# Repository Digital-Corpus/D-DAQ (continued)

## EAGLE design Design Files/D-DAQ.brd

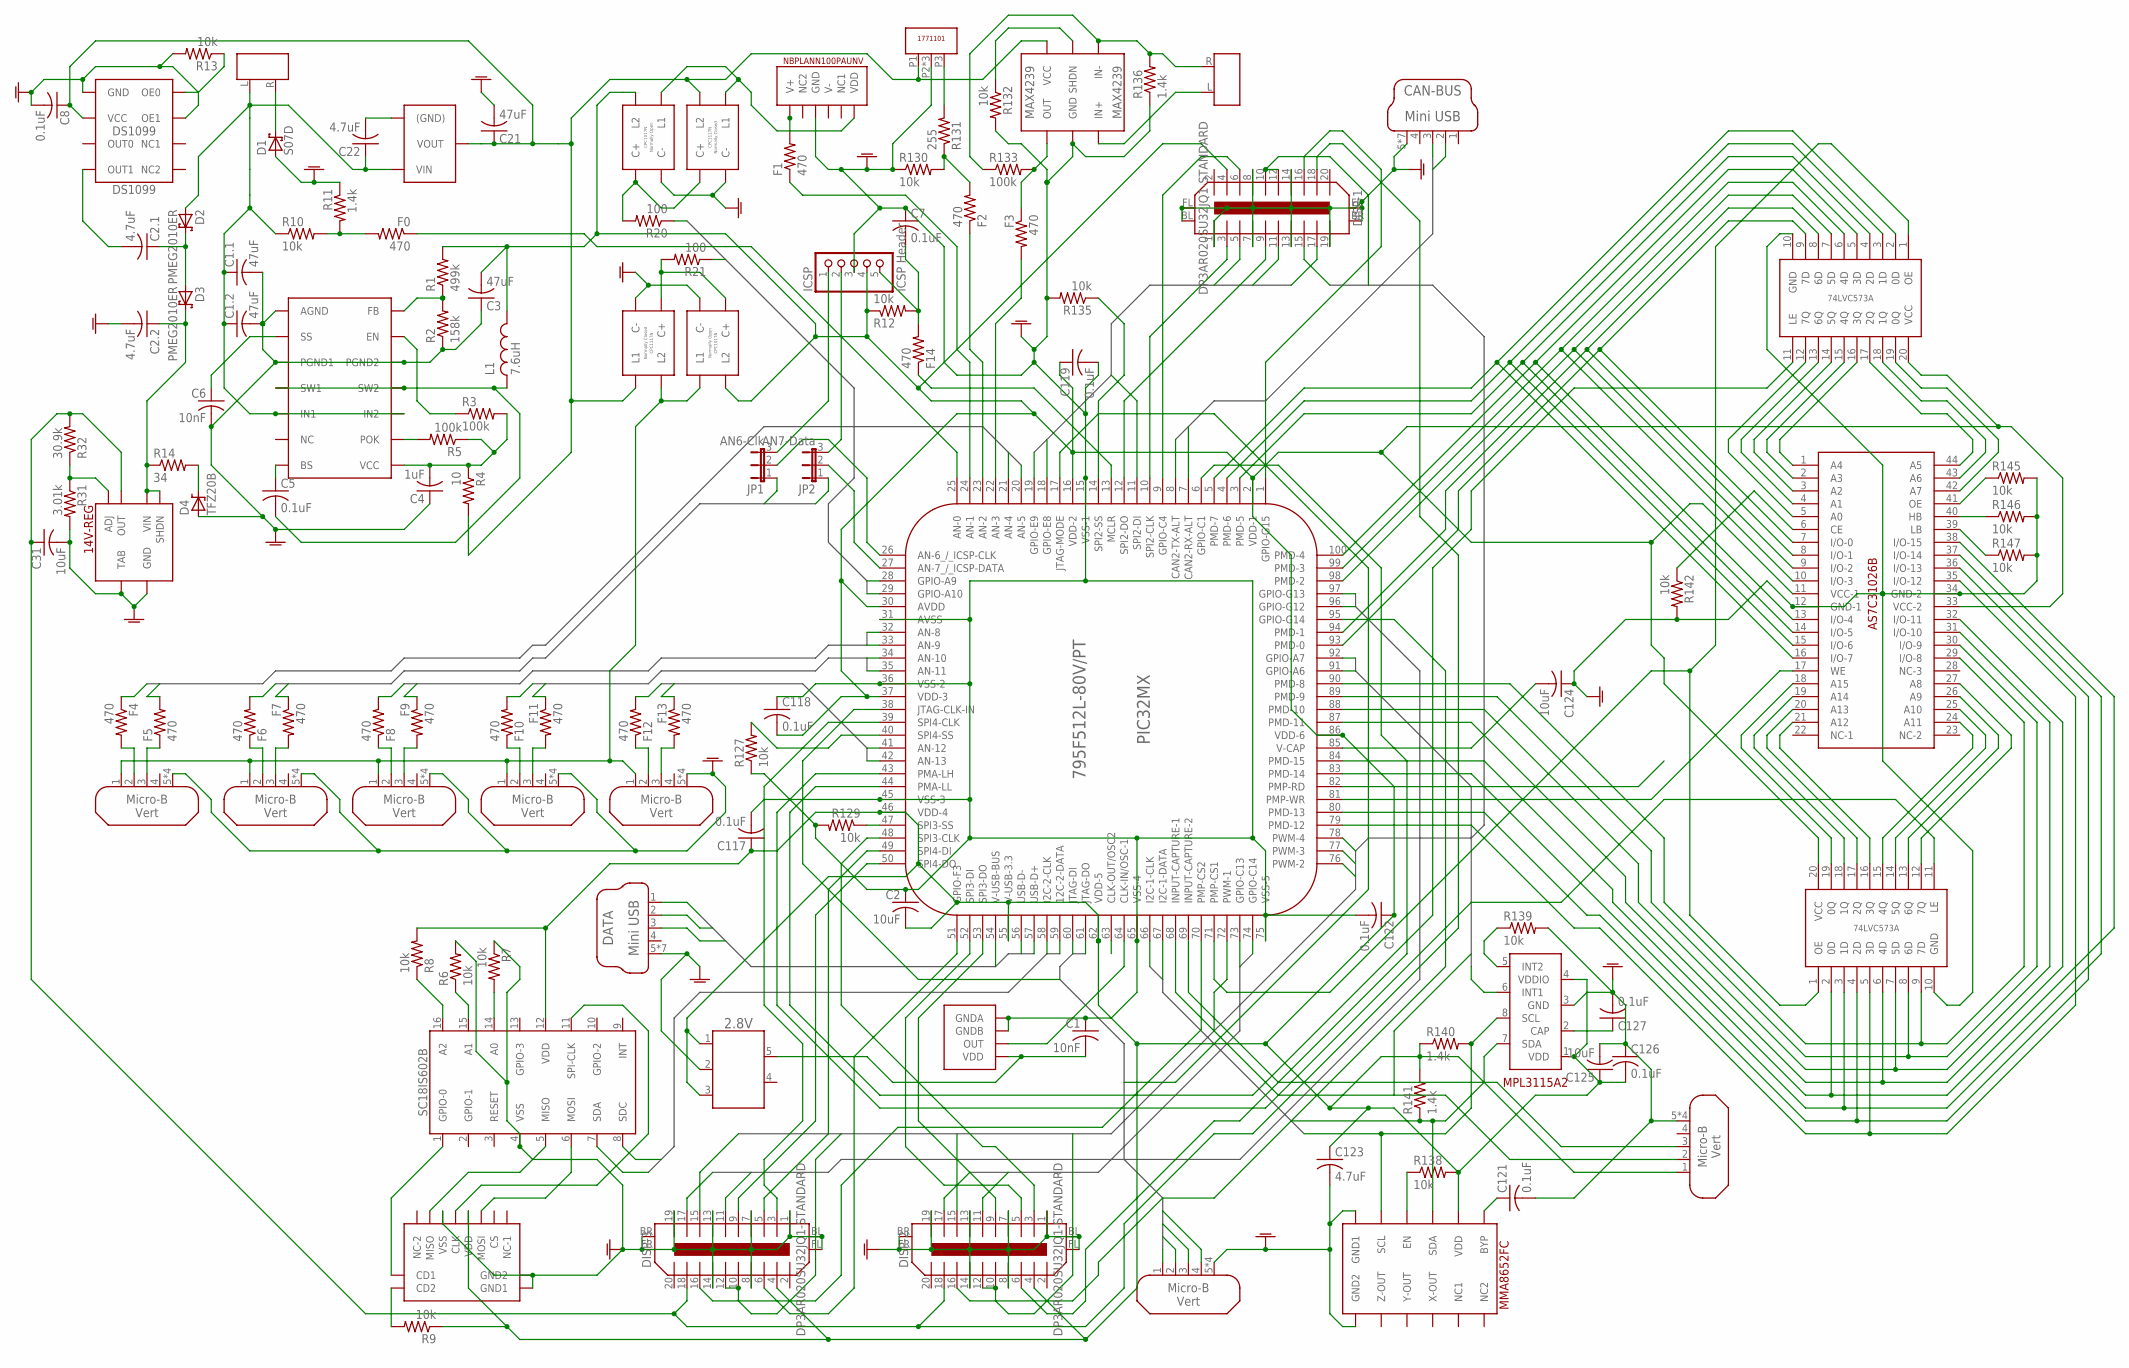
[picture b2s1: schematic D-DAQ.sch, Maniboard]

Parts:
2.8V: TC1016; SOT-23-5
3.3V-TOGGLE-1, 3.3V-TOGGLE-2: NO SSR; SOP-4--CPC1017N
4&5, 6&7, 8&9, 10&11, 12&13: Micro USB; USB-MICRO-B-VERT
5V-REG: ZLDO1117-5.0; SOT-223-5
5V-TOGGLE-1, 5V-TOGGLE-2: NC SSR; SOP-4--CPC1117N
14V-REG: TL1963A-33DCQ; SOT-223-6
AS7C31026B: 1 Mbit SRAM; TSOP-44
AUX-PRESS: PC-1771101
C1, C6: 10nF; C0603K
C1.1, C1.2, C3, C21: 47uF; C1206
C2, C124, C125: 10uF; C0603K
C2.1, C2.2, C22: 4.7uF; C1206
C4: 1uF; C0603K
C5, C7, C8, C117, C118, C119, C121, C122, C126, C127: 0.1uF; C0603K
C31: 10uF; C1206
C123: 4.7uF; C0603K
CAN-BUS: Mini USB; USB-MINI-B-VERT
D1: S07D; SOD-123W
D2, D3: PMEG2010ER; SOD-123W
D4: TFZ20B; TUMD2
DATA: Mini USB; USB-MINI-B-VERT
DISP-1, DISP-2, DISP-3: DP3AR020SU32JQ1-STANDARD
EGT: 1702610; PC-1702610
EGT-AMP: MAX4239; SOT-8
F0, F1, F2, F3, F4, F5, F6, F7, F8, F9, F10, F11, F12, F13, F14: 470; R0603
ICSP: ICSP Header; 1X05
IMP.: Micro USB; USB-MICRO-B-VERT
JP1: AN6-Clk; JP2
JP2: AN7-Data; JP2
JTAG: Micro USB; USB-MICRO-B-VERT
L1: 7.6uH; 7443551XXX
LATCH-HIGH: Octal D-Latch; TSSOP-20
LATCH-LOW: Octal D-Latch; TSSOP-20
MAIN-SMPS: MP2209; QFN-14
MICRO-SD: SCHA4B0400
MMA8652FC: Accelerometer; QFN-12
MPL3115A101: Baro & Temp; LGA-8
NBPLANN100PAUNV: Boost; LEADLESS-SMT
PIC32MX: 795F512L-80V/PT; TQFP-100
POWER: 1702610; PC-1702610
R1: 499k; R0603
R2: 158k; R0603
R3, R5, R133: 100k; R0603
R4: 10; R0603
R6, R7, R8, R9, R10, R12, R13, R127, R129, R130, R132, R135, R138, R139, R142, R145, R146, R147: 10k; R0603
R11, R136, R140, R141: 1.4k; R0603
R14: 34; R0603
R20, R21: 100; R0603
R31: 3.01k; R0603
R32: 30.9k; R0603
R131: 255; R0603
SC18IS602B: I2C to SPI; TSSOP-16
Y1: 16.368 MHz; XTC7009
Y2: DS1099; SOIC-8

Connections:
3.3-&-5V-TOGGLE1: PIC32MX.28 (GPIO-A9), R21.1
3.3-&-5V-TOGGLE2: PIC32MX.29 (GPIO-A10), R20.1
3.3V-RAIL: 2.8V.1 (V-IN), 2.8V.3 (SHDN), 3.3V-TOGGLE-1.4 (L2), 3.3V-TOGGLE-2.4 (L2), AS7C31026B.11 (VCC-1), AS7C31026B.33 (VCC-2), C2.2, C3.2, C117.1, C118.2, C119.1, C122.1, C123.1, C125.1, C126.2, DISP-1.4, DISP-2.4, DISP-3.4, ICSP.4, IMP..1, L1.P$2, LATCH-HIGH.20 (VCC), LATCH-LOW.20 (VCC), MICRO-SD.4 (VDD), MMA8652FC.2 (VDD), MPL3115A101.1 (VDD), MPL3115A101.4 (VDDIO), PIC32MX.2 (VDD-1), PIC32MX.16 (VDD-2), PIC32MX.30 (AVDD), PIC32MX.37 (VDD-3), PIC32MX.46 (VDD-4), PIC32MX.55 (V-USB-3.3), PIC32MX.62 (VDD-5), PIC32MX.86 (VDD-6), R1.2, R8.2, R9.1, R12.1, R138.2, R140.1, R141.2, SC18IS602B.12 (VDD)
5V-ADJ: 5V-REG.ADJ ((GND)), C22.2
5V-RAIL: 5V-REG.VOUT, 5V-REG.VOUT-1 (VOUT), 5V-TOGGLE-1.3 (L1), 5V-TOGGLE-2.4 (L2), AUX-PRESS.P1, C8.1, C21.1, EGT-AMP.6 (VCC), R4.2, Y2.3 (VCC)
12V-BS: C5.1, MAIN-SMPS.7 (BS)
12V-ENABLE: MAIN-SMPS.13 (EN), R3.1
12V-FB: MAIN-SMPS.P14 (FB), R1.1, R2.2
12V-INPUT: 5V-REG.VIN, C1.1.1, C1.2.1, C22.1, D2.P$2, MAIN-SMPS.5 (IN1), MAIN-SMPS.10 (IN2), POWER.L, R10.1
12V-OK: MAIN-SMPS.9 (POK), R5.2
12V-SS: C6.1, MAIN-SMPS.2 (SS)
12V-SW: C5.2, L1.P$1, MAIN-SMPS.4 (SW1), MAIN-SMPS.11 (SW2)
12V-VCC: C4.2, MAIN-SMPS.8 (VCC), R3.2, R4.1, R5.1
14V-12V-DIVIDER: F0.2, R10.2, R11.2
14V-ADJ: 14V-REG.ADJ, R31.1, R32.1
14V-INPUT: 14V-REG.SHDN, 14V-REG.VIN, C2.2.1, D3.P$1, R14.1
14V-RAIL: 14V-REG.VOUT (OUT), C31.1, DISP-1.18, DISP-2.18, DISP-3.18, R32.2
100-PSI-SENSOR-RES: 3.3V-TOGGLE-2.1 (C+), 5V-TOGGLE-2.1 (C+), R20.2
A0-PD: R7.2, SC18IS602B.14 (A0)
A1-PD: R6.1, SC18IS602B.15 (A1)
A2-PU: R8.1, SC18IS602B.16 (A2)
ACCEL-EN: MMA8652FC.4 (EN), R138.1
ADD-0: AS7C31026B.5 (A0), LATCH-LOW.12 (7Q)
ADD-1: AS7C31026B.4 (A1), LATCH-LOW.13 (6Q)
ADD-2: AS7C31026B.3 (A2), LATCH-LOW.14 (5Q)
ADD-3: AS7C31026B.2 (A3), LATCH-LOW.15 (4Q)
ADD-4: AS7C31026B.1 (A4), LATCH-LOW.16 (3Q)
ADD-5: AS7C31026B.44 (A5), LATCH-LOW.17 (2Q)
ADD-6: AS7C31026B.43 (A6), LATCH-LOW.18 (1Q)
ADD-7: AS7C31026B.42 (A7), LATCH-LOW.19 (0Q)
ADD-8: AS7C31026B.27 (A8), LATCH-HIGH.12 (7Q)
ADD-9: AS7C31026B.26 (A9), LATCH-HIGH.13 (6Q)
ADD-10: AS7C31026B.25 (A10), LATCH-HIGH.14 (5Q)
ADD-11: AS7C31026B.24 (A11), LATCH-HIGH.15 (4Q)
ADD-12: AS7C31026B.21 (A12), LATCH-HIGH.16 (3Q)
ADD-13: AS7C31026B.20 (A13), LATCH-HIGH.17 (2Q)
ADD-14: AS7C31026B.19 (A14), LATCH-HIGH.18 (1Q)
ADD-15: AS7C31026B.18 (A15), LATCH-HIGH.19 (0Q)
AN0-VOLT: F0.1, PIC32MX.25 (AN-0)
AN1-BOOST: F1.1, PIC32MX.24 (AN-1)
AN2-OIL-PESS: F2.1, PIC32MX.23 (AN-2)
AN3-EGT: F3.2, PIC32MX.22 (AN-3)
AN4: 4&5.2, F4.2
AN5: 4&5.3, F5.1
AN6: 6&7.2, F6.1
AN7: 6&7.3, F7.2
AN8: 8&9.2, F8.1
AN9: 8&9.3, F9.2
AN10: 10&11.2, F10.1
AN11: 10&11.3, F11.2
AN12: 12&13.2, F12.1
AN13: 12&13.3, F13.2
AUTO-DETECT: 3.3V-TOGGLE-1.1 (C+), 5V-TOGGLE-1.1 (C+), R21.2
AUX-OUT: F2.2, R130.2, R131.1
BARO-INT2: MPL3115A101.5 (INT2), R139.1
BOOST-OUT: F1.2, NBPLANN100PAUNV.6 (V+)
BOOST-PWR: 3.3V-TOGGLE-2.3 (L1), 5V-TOGGLE-2.3 (L1), NBPLANN100PAUNV.1 (VDD)
CAN-BUS1: CAN-BUS.2, PIC32MX.8 (CAN2-TX-ALT)
CAN-BUS2: CAN-BUS.3, PIC32MX.7 (CAN2-RX-ALT)
CARD-DETECT: MICRO-SD.G3 (CD1), SC18IS602B.1 (GPIO-0)
CE: AS7C31026B.6 (CE), R142.1
CHARG-CAPS: C2.1.2, Y2.1 (OUT1)
CP-PUMP: C2.1.1, D2.P$1, D3.P$2
CPS-INPUT: IMP..2, PIC32MX.68 (INPUT-CAPTURE-1)
CRYSTAL-OUT: PIC32MX.63 (CLK-OUT/OSC2)
DISP1-B1: DISP-1.5, PIC32MX.11 (SPI2-DI)
DISP1-B2: DISP-1.11, PIC32MX.18 (GPIO-E8)
DISP1-B3: DISP-1.17, PIC32MX.19 (GPIO-E9)
DISP2-B1: DISP-2.5, PIC32MX.52 (SPI3-DI)
DISP2-B2: DISP-2.11, PIC32MX.73 (GPIO-C13)
DISP2-B3: DISP-2.17, PIC32MX.74 (GPIO-C14)
DISP2-RS: DISP-2.16, PIC32MX.95 (GPIO-G14)
DISP3-B1: DISP-3.5, PIC32MX.49 (SPI4-DI)
DISP3-B2: DISP-3.11, PIC32MX.96 (GPIO-G12)
DISP3-B3: DISP-3.17, PIC32MX.97 (GPIO-G13)
DISP3-RS: DISP-1.16, PIC32MX.1 (GPIO-G15)
DISP-1_HPD: DISP-1.6, PIC32MX.9 (GPIO-C4)
DISP-HPD2: DISP-2.6, PIC32MX.6 (GPIO-C1)
DISP-HPD3: DISP-3.6, PIC32MX.51 (GPIO-F3)
EGT-NEG-IN: EGT.R, EGT-AMP.4 (IN-), R133.1, R136.2
EGT-OUT: EGT-AMP.1 (OUT), F3.1, R133.2
EGT-POS-IN: EGT.L, EGT-AMP.3 (IN+)
EGT-SHTDWN: EGT-AMP.5 (SHDN), R132.1
GND: 2.8V.2 (GND), 3.3V-TOGGLE-1.2 (C-), 3.3V-TOGGLE-2.2 (C-), 4&5.5, 4&5.T0 (5), 4&5.T1 (5), 4&5.T2 (5), 5V-TOGGLE-1.2 (C-), 5V-TOGGLE-2.2 (C-), 6&7.5, 6&7.T0 (5), 6&7.T1 (5), 6&7.T2 (5), 8&9.5, 8&9.T0 (5), 8&9.T1 (5), 8&9.T2 (5), 10&11.5, 10&11.T0 (5), 10&11.T1 (5), 10&11.T2 (5), 12&13.5, 12&13.T0 (5), 12&13.T1 (5), 12&13.T2 (5), 14V-REG.GND, 14V-REG.TAB, AS7C31026B.12 (GND-1), AS7C31026B.34 (GND-2), AUX-PRESS.P2, AUX-PRESS.T0, AUX-PRESS.T1, C1.1, C1.1.2, C1.2.2, C2.1, C2.2.2, C3.1, C4.1, C6.2, C7.1, C8.2, C21.2, C31.2, C117.2, C118.1, C119.2, C121.2, C122.2, C123.2, C124.1, C125.2, C126.1, C127.2, CAN-BUS.5, CAN-BUS.P$1, CAN-BUS.P$2, CAN-BUS.P$3, CAN-BUS.P$4, CAN-BUS.T0, CAN-BUS.T1, D1.P$2, D4.P$1 (A), DATA.5, DATA.P$1, DATA.P$2, DATA.P$3, DATA.P$4, DATA.T0, DATA.T1, DISP-1.1, DISP-1.7, DISP-1.8, DISP-1.13, DISP-1.14, DISP-1.19, DISP-1.BL, DISP-1.BR, DISP-1.FL, DISP-1.FR, DISP-2.1, DISP-2.7, DISP-2.8, DISP-2.13, DISP-2.14, DISP-2.19, DISP-2.BL, DISP-2.BR, DISP-2.FL, DISP-2.FR, DISP-3.1, DISP-3.7, DISP-3.8, DISP-3.13, DISP-3.14, DISP-3.19, DISP-3.BL, DISP-3.BR, DISP-3.FL, DISP-3.FR, EGT-AMP.2 (GND), ICSP.3, IMP..5, IMP..T0 (5), IMP..T1 (5), IMP..T2 (5), JTAG.5, JTAG.T0 (5), JTAG.T1 (5), JTAG.T2 (5), LATCH-HIGH.10 (GND), LATCH-LOW.10 (GND), MAIN-SMPS.1 (AGND), MAIN-SMPS.3 (PGND1), MAIN-SMPS.12 (PGND2), MAIN-SMPS.P$15 (AGND), MICRO-SD.6 (VSS), MICRO-SD.G1 (GND1), MICRO-SD.G2 (GND2), MMA8652FC.6 (GND1), MMA8652FC.7 (GND2), MPL3115A101.3 (GND), NBPLANN100PAUNV.4 (GND), PIC32MX.15 (VSS-1), PIC32MX.31 (AVSS), PIC32MX.36 (VSS-2), PIC32MX.45 (VSS-3), PIC32MX.65 (VSS-4), PIC32MX.75 (VSS-5), R2.1, R6.2, R7.1, R11.1, R13.2, R31.2, R127.1, R129.2, R130.1, R132.2, R135.2, R136.1, R139.2, R142.2, R145.2, R146.2, R147.2, SC18IS602B.4 (VSS), Y1.P$1 (GNDA), Y1.P$2 (GNDB), Y2.4 (GND), Y2.6 (OE1)
HB: AS7C31026B.40 (HB), R146.1
I2C-INT-BUS-PIN1: MPL3115A101.6 (INT1), PIC32MX.91 (GPIO-A6)
I2C-INT-BUS-PIN2: PIC32MX.92 (GPIO-A7)
I2C-PIN1: MMA8652FC.5 (SCL), MPL3115A101.8 (SCL), PIC32MX.66 (I2C-1-CLK), R140.2
I2C-PIN2: MMA8652FC.3 (SDA), MPL3115A101.7 (SDA), PIC32MX.67 (I2C-1-DATA), R141.1
I2C-SD-PIN1: PIC32MX.58 (I2C-2-CLK), SC18IS602B.8 (SDC)
I2C-SD-PIN2: PIC32MX.59 (12C-2-DATA), SC18IS602B.7 (SDA)
ICSP-CLK: ICSP.1, JP1.3
ICSP-DATA: ICSP.2, JP2.3
ICSP-MCLR: C7.2, F14.2, ICSP.5, R12.2
INPUT-6_/_ICSP-CLK: JP1.2, PIC32MX.26 (AN-6_/_ICSP-CLK)
INPUT-7_/_ICSP-DATA: JP2.2, PIC32MX.27 (AN-7_/_ICSP-DATA)
JTAG-PIN-1: JTAG.1, PIC32MX.17 (JTAG-MODE)
JTAG-PIN-2: JTAG.2, PIC32MX.38 (JTAG-CLK-IN)
JTAG-PIN-3: JTAG.3, PIC32MX.60 (JTAG-DI)
JTAG-PIN-4: JTAG.4, PIC32MX.61 (JTAG-DO)
LB: AS7C31026B.39 (LB), R147.1
LNS-INPUT: IMP..3, PIC32MX.69 (INPUT-CAPTURE-2)
MCLR: F14.1, PIC32MX.13 (MCLR)
MPL-BYP-CAP: C127.1, MPL3115A101.2 (CAP)
unnamed: C121.1, MMA8652FC.1 (BYP)
OE: AS7C31026B.41 (OE), R145.1
OE0: R13.1, Y2.5 (OE0)
OIL-PRESS-OUT: AUX-PRESS.P3, R131.2
OSC-PWR: 2.8V.5 (V-OUT), C1.2, Y1.P$4 (VDD)
OSC-SIG: PIC32MX.64 (CLK-IN/OSC-1), Y1.P$3 (OUT)
P$1: CAN-BUS.1
PMA-CS2: DISP-3.16, PIC32MX.70 (PMP-CS2)
PMA-HL: LATCH-HIGH.11 (LE), PIC32MX.43 (PMA-LH)
PMA-LL: LATCH-LOW.11 (LE), PIC32MX.44 (PMA-LL)
PMD0: AS7C31026B.7 (I/O-0), LATCH-LOW.9 (7D), PIC32MX.93 (PMD-0)
PMD1: AS7C31026B.8 (I/O-1), LATCH-LOW.8 (6D), PIC32MX.94 (PMD-1)
PMD2: AS7C31026B.9 (I/O-2), LATCH-LOW.7 (5D), PIC32MX.98 (PMD-2)
PMD3: AS7C31026B.10 (I/O-3), LATCH-LOW.6 (4D), PIC32MX.99 (PMD-3)
PMD4: AS7C31026B.13 (I/O-4), LATCH-LOW.5 (3D), PIC32MX.100 (PMD-4)
PMD5: AS7C31026B.14 (I/O-5), LATCH-LOW.4 (2D), PIC32MX.3 (PMD-5)
PMD6: AS7C31026B.15 (I/O-6), LATCH-LOW.3 (1D), PIC32MX.4 (PMD-6)
PMD7: AS7C31026B.16 (I/O-7), LATCH-LOW.2 (0D), PIC32MX.5 (PMD-7)
PMD8: AS7C31026B.29 (I/O-8), LATCH-HIGH.9 (7D), PIC32MX.90 (PMD-8)
PMD9: AS7C31026B.30 (I/O-9), LATCH-HIGH.8 (6D), PIC32MX.89 (PMD-9)
PMD10: AS7C31026B.31 (I/O-10), LATCH-HIGH.7 (5D), PIC32MX.88 (PMD-10)
PMD11: AS7C31026B.32 (I/O-11), LATCH-HIGH.6 (4D), PIC32MX.87 (PMD-11)
PMD12: AS7C31026B.35 (I/O-12), LATCH-HIGH.5 (3D), PIC32MX.79 (PMD-12)
PMD13: AS7C31026B.36 (I/O-13), LATCH-HIGH.4 (2D), PIC32MX.80 (PMD-13)
PMD15: AS7C31026B.38 (I/O-15), LATCH-HIGH.2 (0D), PIC32MX.84 (PMD-15)
PMD-14: AS7C31026B.37 (I/O-14), LATCH-HIGH.3 (1D), PIC32MX.83 (PMD-14)
PMD-READ: PIC32MX.82 (PMP-RD)
PMP-CS1: LATCH-HIGH.1 (OE), LATCH-LOW.1 (OE), PIC32MX.71 (PMP-CS1)
PMP-WRITE: AS7C31026B.17 (WE), PIC32MX.81 (PMP-WR)
PWM1: DISP-3.15, PIC32MX.72 (PWM-1)
PWM2: DISP-2.15, PIC32MX.76 (PWM-2)
PWM3: DISP-1.15, PIC32MX.77 (PWM-3)
PWM4: DISP-1.10, DISP-1.12, DISP-2.10, DISP-2.12, DISP-3.10, DISP-3.12, PIC32MX.78 (PWM-4)
PWR-GND: D1.P$1, POWER.R
SD-MISO: MICRO-SD.7 (MISO), SC18IS602B.5 (MISO)
SD-MOSI: MICRO-SD.3 (MOSI), SC18IS602B.6 (MOSI)
SD-PULL-DOWN: MICRO-SD.G4 (CD2), R9.2
SD-SPI-CLK: MICRO-SD.5 (CLK), SC18IS602B.11 (SPI-CLK)
SENSOR_PAIR_AN4: F4.1, PIC32MX.21 (AN-4)
SENSOR_PAIR_AN5: F5.2, PIC32MX.20 (AN-5)
SENSOR_PAIR_AN6: F6.2, JP1.1
SENSOR_PAIR_AN7: F7.1, JP2.1
SENSOR_PAIR_AN8: F8.2, PIC32MX.32 (AN-8)
SENSOR_PAIR_AN9: F9.1, PIC32MX.33 (AN-9)
SENSOR_PAIR_AN10: F10.2, PIC32MX.34 (AN-10)
SENSOR_PAIR_AN11: F11.1, PIC32MX.35 (AN-11)
SENSOR_PAIR_AN12: F12.2, PIC32MX.41 (AN-12)
SENSOR_PAIR_AN13: F13.1, PIC32MX.42 (AN-13)
SHUNT: D4.P$2 (C), R14.2
SPI2-CLK: DISP-1.3, PIC32MX.10 (SPI2-CLK)
SPI2-DATA: DISP-1.9, PIC32MX.12 (SPI2-DO)
SPI2-SS: PIC32MX.14 (SPI2-SS), R135.1
SPI3-CLK: DISP-2.3, PIC32MX.48 (SPI3-CLK)
SPI3-DATA: DISP-2.9, PIC32MX.53 (SPI3-DO)
SPI3-SS: PIC32MX.47 (SPI3-SS), R129.1
SPI4-CLK: DISP-3.3, PIC32MX.39 (SPI4-CLK)
SPI4-DATA: DISP-3.9, PIC32MX.50 (SPI4-DO)
SPI4-SS: PIC32MX.40 (SPI4-SS), R127.2
USB-PIN1: DATA.1, PIC32MX.54 (V-USB-BUS)
USB-PIN2: DATA.2, PIC32MX.56 (USB-D-)
USB-PIN3: DATA.3, PIC32MX.57 (USB-D+)
USB-PWR: 3.3V-TOGGLE-1.3 (L1), 4&5.1, 5V-TOGGLE-1.4 (L2), 6&7.1, 8&9.1, 10&11.1, 12&13.1
V-CAP: C124.2, PIC32MX.85 (V-CAP)

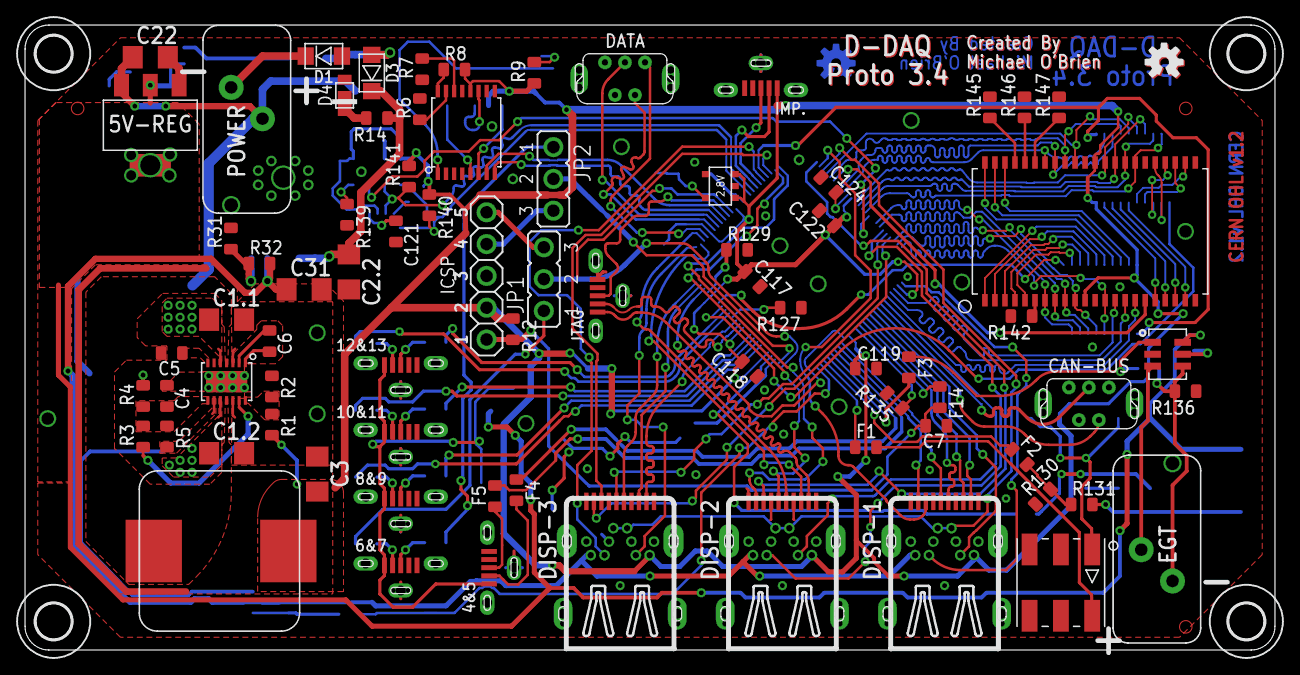
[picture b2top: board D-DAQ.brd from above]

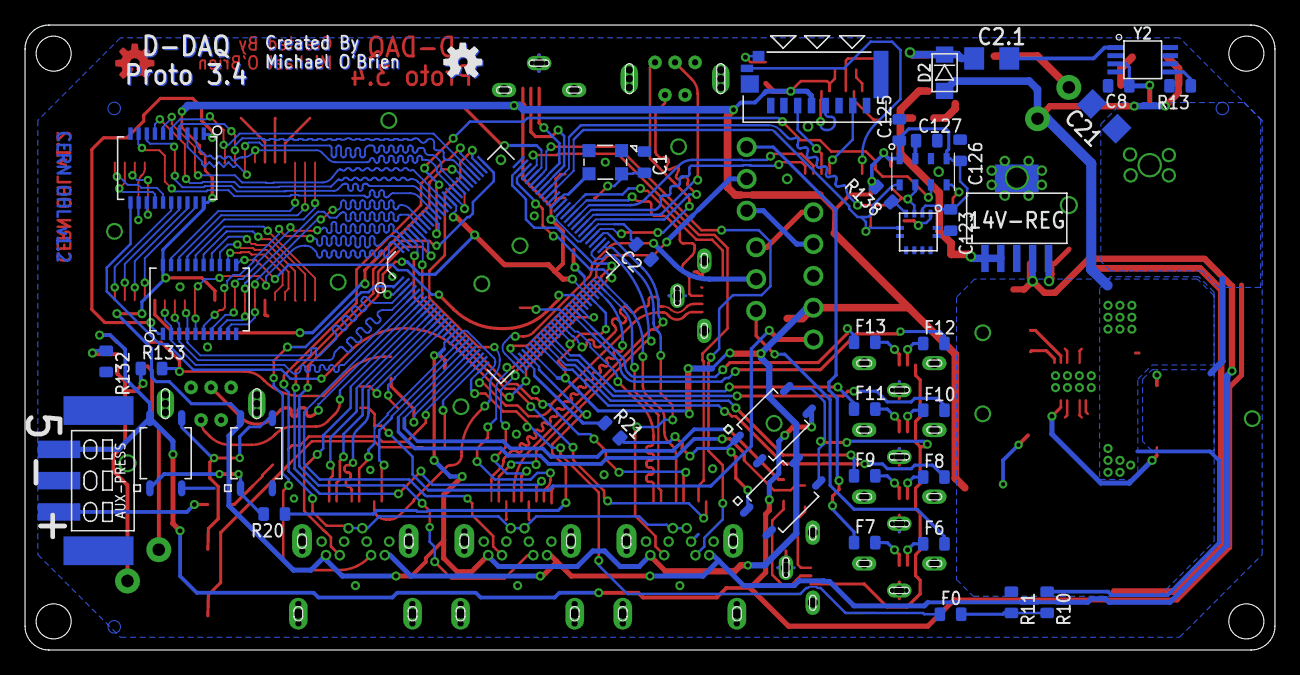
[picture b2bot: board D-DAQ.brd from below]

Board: 2 copper layers, 99.8 x 49.9 mm, 123 parts (42 on the bottom side), 163 nets.

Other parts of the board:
U$2, U$3, U$4, U$5: 2,8
U$6, U$7: OSHW-LOGO-S

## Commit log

2014-05-16 D-DAQ begins
2014-05-16 Create README.md
    Testing with sync between website and server...
2014-05-16 Updating files server-side
2014-05-16 Uploading current stale state of code
2014-05-16 Consolidate
2014-05-16 change readme to be a bit more accurate
2014-07-02 hardware design files and license upload of 'Proto v3.4' of the mainboard
2014-07-04 actually add the files...
2014-07-04 remove old .dsn for freerouting.net...
2014-07-11 Update to Proto v3.6. Please visit the following for details: http://hackaday.io/project/964/log/4782
2014-07-11 v3.6.1 No major changes, just cleanup and moving to Eagle v6.6 files
2014-07-11 v3.6.2 Fixed fiducial solder mask
2014-07-13 v3.6.2: http://hackaday.io/project/964/log/4782
2014-07-13 cleanup
2014-07-15 v3.6.5 - Package & placement tweaks to design files and then permissions changes due to new system local copies reside
2014-07-15 update component values
2014-07-23 Prototype revision 4 of the schematic capture: http://hackaday.io/project/964/log/5368
2014-09-19 Updating to Proto 4
